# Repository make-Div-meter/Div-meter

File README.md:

# 概要
ゲーム・アニメ作品「STEINS;GATE（シュタインズ・ゲート）」に登場する「世界線変動率計測器≪ダイバージェンスメーター≫」を製作する。

## 開発スケジュール
### 第1段階　2020年3月31日
ニキシー管に任意の数字を表示できる状態にする。

### 第2段階
時計・カレンダー機能の実装。

### 第3段階
外部端末とBluetooth等の無線通信を用いて接続し、任意に表示を変化させることができる。

## 表示モード
複数の機能を持たせる。
### DGモード
劇中に登場するダイバージェンスメーターと同じように世界線変動率を8桁のニキシー管に表示する。
### 時計モード
時計としての表示を行う。
表示フォーマットは「HH.mm.ss」
### カレンダーモード
カレンダーとしての表示を行う。
表示フォーマットは「MM.dd...」

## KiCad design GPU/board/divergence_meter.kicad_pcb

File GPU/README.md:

# GPU
ニキシー管をダイナミック点灯させるマイコン
CPUとシリアル通信を行い，内部レジスタに値を保存する。またその内容をニキシー管に表示する．内部レジスタに保存した値はCPUから新しい値が送られてくるまで表示され続ける。

## 要求スペック
### 動作クロック
未定
### ピン数
ニキシー管制御　3+4
I2C　2
UART 2
## 動作電圧
3.3V

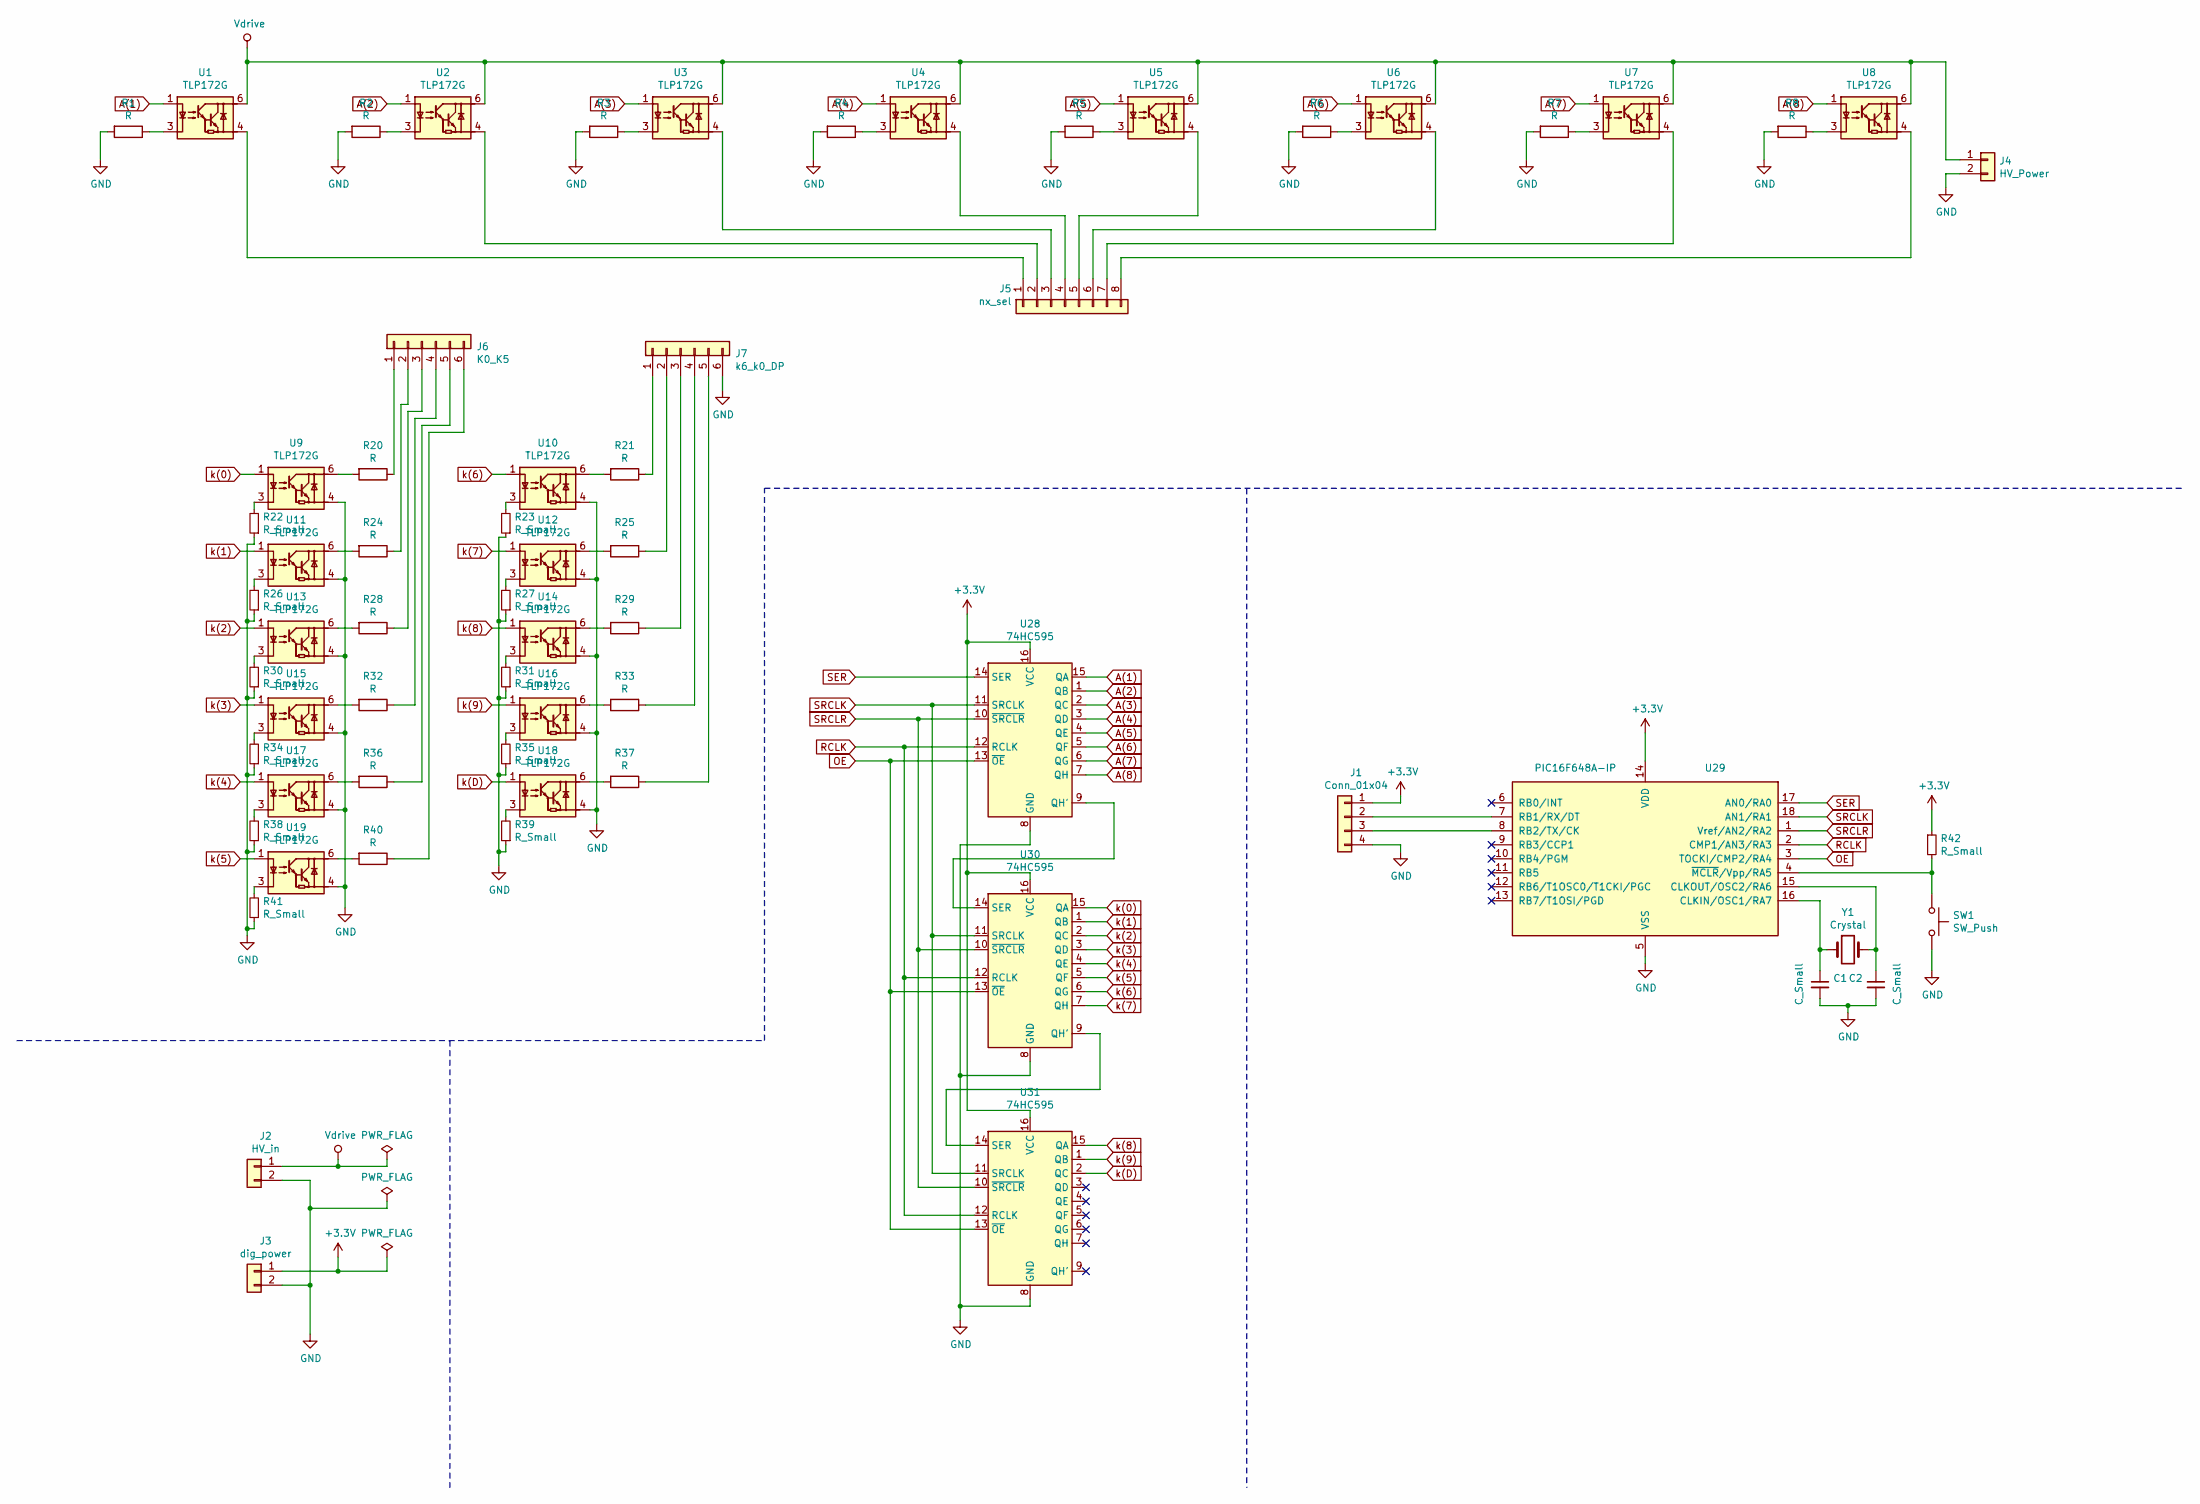
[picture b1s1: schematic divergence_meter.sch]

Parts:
C1, C2: C_Small; C_0603_1608Metric_Pad1.05x0.95mm_HandSolder
J1: Conn_01x04; PinHeader_1x04_P2.54mm_Vertical
J2: HV_in; PinHeader_1x02_P2.54mm_Vertical
J3: dig_power; PinHeader_1x02_P2.54mm_Vertical
J4: HV_Power; PinHeader_1x02_P2.54mm_Vertical
J5: nx_sel; PinHeader_1x08_P2.54mm_Vertical
J6: K0_K5; PinHeader_1x06_P2.54mm_Vertical
J7: k6_k0_DP; PinHeader_1x06_P2.54mm_Vertical
R1, R2, R3, R4, R5, R6, R7, R8, R20, R21, R24, R25, R28, R29, R32, R33, R36, R37, R40: R; R_0603_1608Metric_Pad1.05x0.95mm_HandSolder
R22, R23, R26, R27, R30, R31, R34, R35, R38, R39, R41, R42: R_Small; R_0603_1608Metric_Pad1.05x0.95mm_HandSolder
SW1: SW_Push; SW_PUSH_6mm_H5mm
U1, U2, U3, U4, U5, U6, U7, U8, U9, U10, U11, U12, U13, U14, U15, U16, U17, U18, U19: TLP172G; DIP-5-6_W8.89mm_SMDSocket_LongPads
U28, U30, U31: 74HC595; SOP-16_4.55x10.3mm_P1.27mm
U29: PIC16F648A-IP; SOIC-18W_7.5x11.6mm_P1.27mm
Y1: Crystal; Crystal_SMD_HC49-SD_HandSoldering

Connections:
+3V3: J1.1, J3.1, R42.1, U28.16 (VCC), U29.14 (VDD), U30.16 (VCC), U31.16 (VCC)
A(1): U1.1, U28.15 (QA)
A(2): U2.1, U28.1 (QB)
A(3): U3.1, U28.2 (QC)
A(4): U4.1, U28.3 (QD)
A(5): U5.1, U28.4 (QE)
A(6): U6.1, U28.5 (QF)
A(7): U7.1, U28.6 (QG)
A(8): U8.1, U28.7 (QH)
GND: C1.2, C2.2, J1.4, J2.2, J3.2, J4.2, J7.6, R1.2, R2.2, R3.2, R4.2, R5.2, R6.2, R7.2, R8.2, R22.1, R23.1, R26.1, R27.1, R30.1, R31.1, R34.1, R35.1, R38.1, R39.1, R41.1, SW1.2, U9.4, U10.4, U11.4, U12.4, U13.4, U14.4, U15.4, U16.4, U17.4, U18.4, U19.4, U28.8 (GND), U29.5 (VSS), U30.8 (GND), U31.8 (GND)
unnamed: C1.1, U29.16 (CLKIN/OSC1/RA7), Y1.1
unnamed: C2.1, U29.15 (CLKOUT/OSC2/RA6), Y1.2
unnamed: J1.2, U29.7 (RB1/RX/DT)
unnamed: J1.3, U29.8 (RB2/TX/CK)
unnamed: J5.1, U1.4
unnamed: J5.2, U2.4
unnamed: J5.3, U3.4
unnamed: J5.4, U4.4
unnamed: J5.5, U5.4
unnamed: J5.6, U6.4
unnamed: J5.7, U7.4
unnamed: J5.8, U8.4
unnamed: J6.1, R20.1
unnamed: J6.2, R24.1
unnamed: J6.3, R28.1
unnamed: J6.4, R32.1
unnamed: J6.5, R36.1
unnamed: J6.6, R40.1
unnamed: J7.1, R21.1
unnamed: J7.2, R25.1
unnamed: J7.3, R29.1
unnamed: J7.4, R33.1
unnamed: J7.5, R37.1
unnamed: R1.1, U1.3
unnamed: R2.1, U2.3
unnamed: R3.1, U3.3
unnamed: R4.1, U4.3
unnamed: R5.1, U5.3
unnamed: R6.1, U6.3
unnamed: R7.1, U7.3
unnamed: R8.1, U8.3
unnamed: R20.2, U9.6
unnamed: R21.2, U10.6
unnamed: R22.2, U9.3
unnamed: R23.2, U10.3
unnamed: R24.2, U11.6
unnamed: R25.2, U12.6
unnamed: R26.2, U11.3
unnamed: R27.2, U12.3
unnamed: R28.2, U13.6
unnamed: R29.2, U14.6
unnamed: R30.2, U13.3
unnamed: R31.2, U14.3
unnamed: R32.2, U15.6
unnamed: R33.2, U16.6
unnamed: R34.2, U15.3
unnamed: R35.2, U16.3
unnamed: R36.2, U17.6
unnamed: R37.2, U18.6
unnamed: R38.2, U17.3
unnamed: R39.2, U18.3
unnamed: R40.2, U19.6
unnamed: R41.2, U19.3
unnamed: R42.2, SW1.1, U29.4 (~MCLR~/Vpp/RA5)
unnamed: U28.9 (QH'), U30.14 (SER)
unnamed: U30.9 (QH'), U31.14 (SER)
OE: U28.13 (~OE), U29.3 (TOCKI/CMP2/RA4), U30.13 (~OE), U31.13 (~OE)
RCLK: U28.12 (RCLK), U29.2 (CMP1/AN3/RA3), U30.12 (RCLK), U31.12 (RCLK)
SER: U28.14 (SER), U29.17 (AN0/RA0)
SRCLK: U28.11 (SRCLK), U29.18 (AN1/RA1), U30.11 (SRCLK), U31.11 (SRCLK)
SRCLR: U28.10 (~SRCLR), U29.1 (Vref/AN2/RA2), U30.10 (~SRCLR), U31.10 (~SRCLR)
Vdrive: J2.1, J4.1, U1.6, U2.6, U3.6, U4.6, U5.6, U6.6, U7.6, U8.6
k(0): U9.1, U30.15 (QA)
k(1): U11.1, U30.1 (QB)
k(2): U13.1, U30.2 (QC)
k(3): U15.1, U30.3 (QD)
k(4): U17.1, U30.4 (QE)
k(5): U19.1, U30.5 (QF)
k(6): U10.1, U30.6 (QG)
k(7): U12.1, U30.7 (QH)
k(8): U14.1, U31.15 (QA)
k(9): U16.1, U31.1 (QB)
k(D): U18.1, U31.2 (QC)

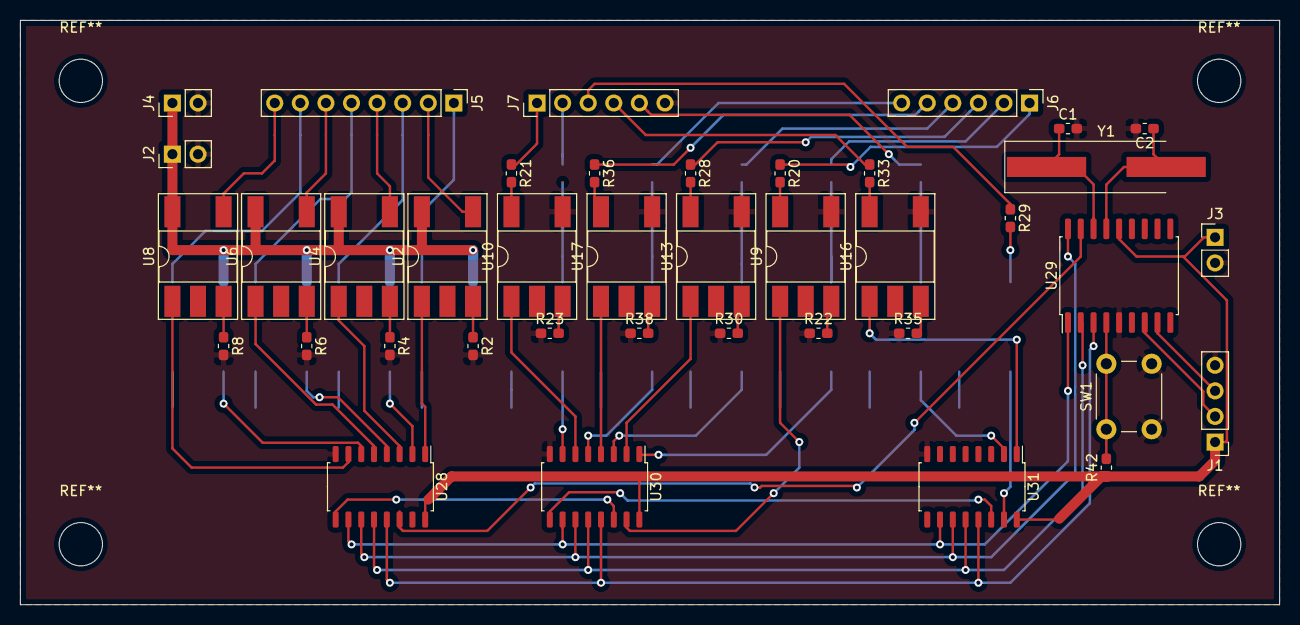
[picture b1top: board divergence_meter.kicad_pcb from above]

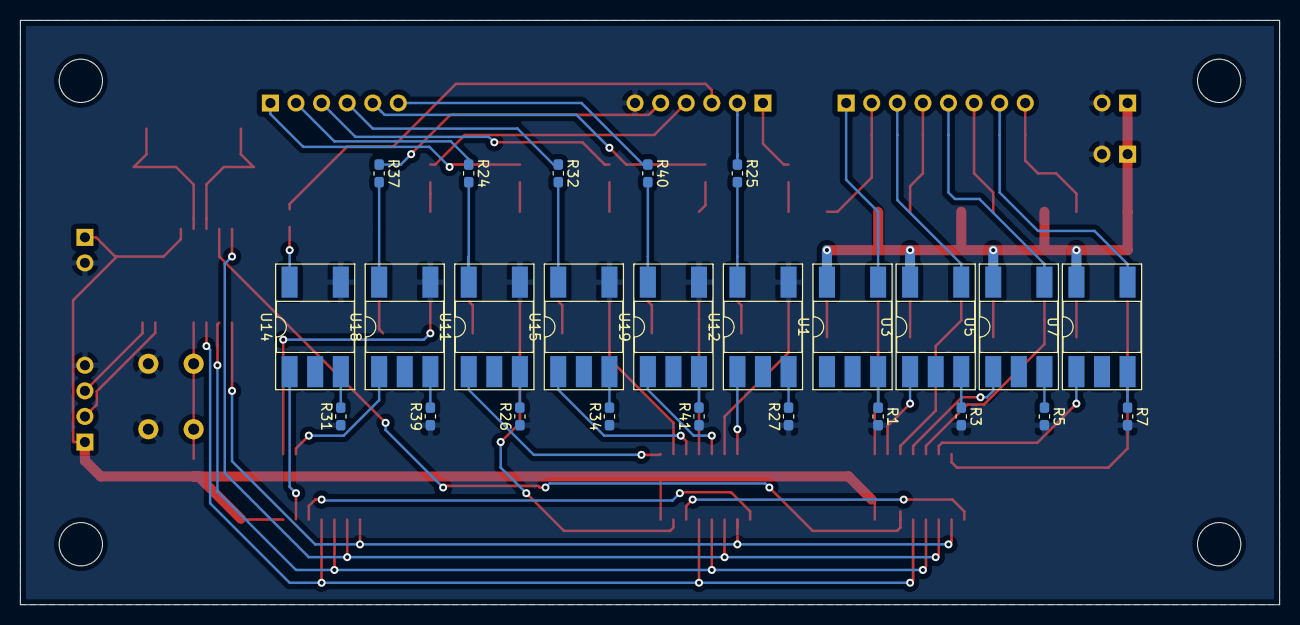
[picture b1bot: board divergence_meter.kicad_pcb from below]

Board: 2 copper layers, 125.0 x 58.0 mm, 65 parts (25 on the bottom side), 83 nets.

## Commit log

2020-02-09 test
2020-02-09 test_16:32
2020-02-09 app readme
2020-02-09 readme
2020-02-09 02/09 20:10
2020-02-12 add GPU.h
2020-03-03 2020/03/03 19:58 kicadプロジェクトを追加 GPU基板とニキシーマウント基板が統合されている
2020-03-31 2020/03/31 DC/DC and GPU added
2020-03-31 2020/03/31 DC/DC SMD
